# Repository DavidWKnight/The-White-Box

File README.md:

# The White Box
The White Box is a digital effect pedal for guitar and bass. It does standard effects processing such as distortion, delays, and other time based effects. Most of these effects are currently implemented in individual effect pedals, this project is attempting to put merge all these effects into a single multi effects pedal. Documentation how the design works can be found in /Documentation, The schematics for the PCB's can be found in /Hardware, and code for the processors can be found in /Software.

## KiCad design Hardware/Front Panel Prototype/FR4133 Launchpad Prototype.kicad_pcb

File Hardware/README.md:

# Hardware
The user interface is a 4x20 LCD character display, with 8 buttons and 4 knobs to interact with. These are driven by the MSP430FR45969 microcontroller which will be on a PCB referenced in the project as the "Front Panel". The front panel only deals with the user inteface and it connects to another PCB called the "Main Board" that handles all the signal processing. Signal processing is done by the C5535 DSP with the AIC3204 audio codec handling audio IO. The front panel and main board are connected by board-to-board connectors carrying 3.3v power, ground, and an SPI bus for the FR5969 and C5535 to communicate.

# CAD
Both the front panel and main board are designed using kicad which is a free PCB design suite (http://kicad-pcb.org/). Each board folder contains standard kicad project files as well as a Component Library for the custom components i've made. In each folder is also a pdf show the latest version of the schematic.

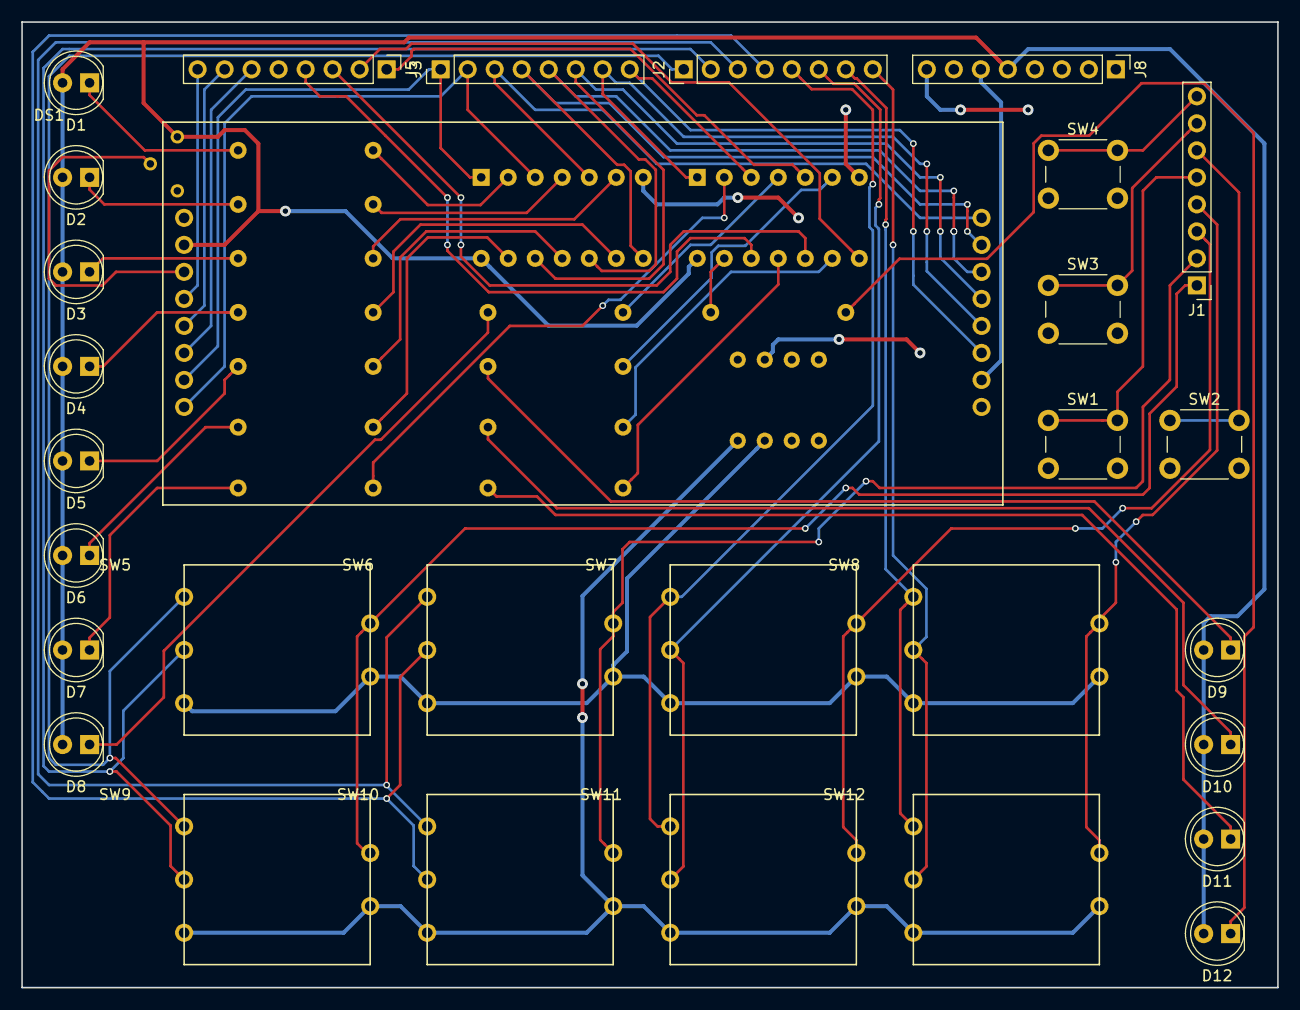
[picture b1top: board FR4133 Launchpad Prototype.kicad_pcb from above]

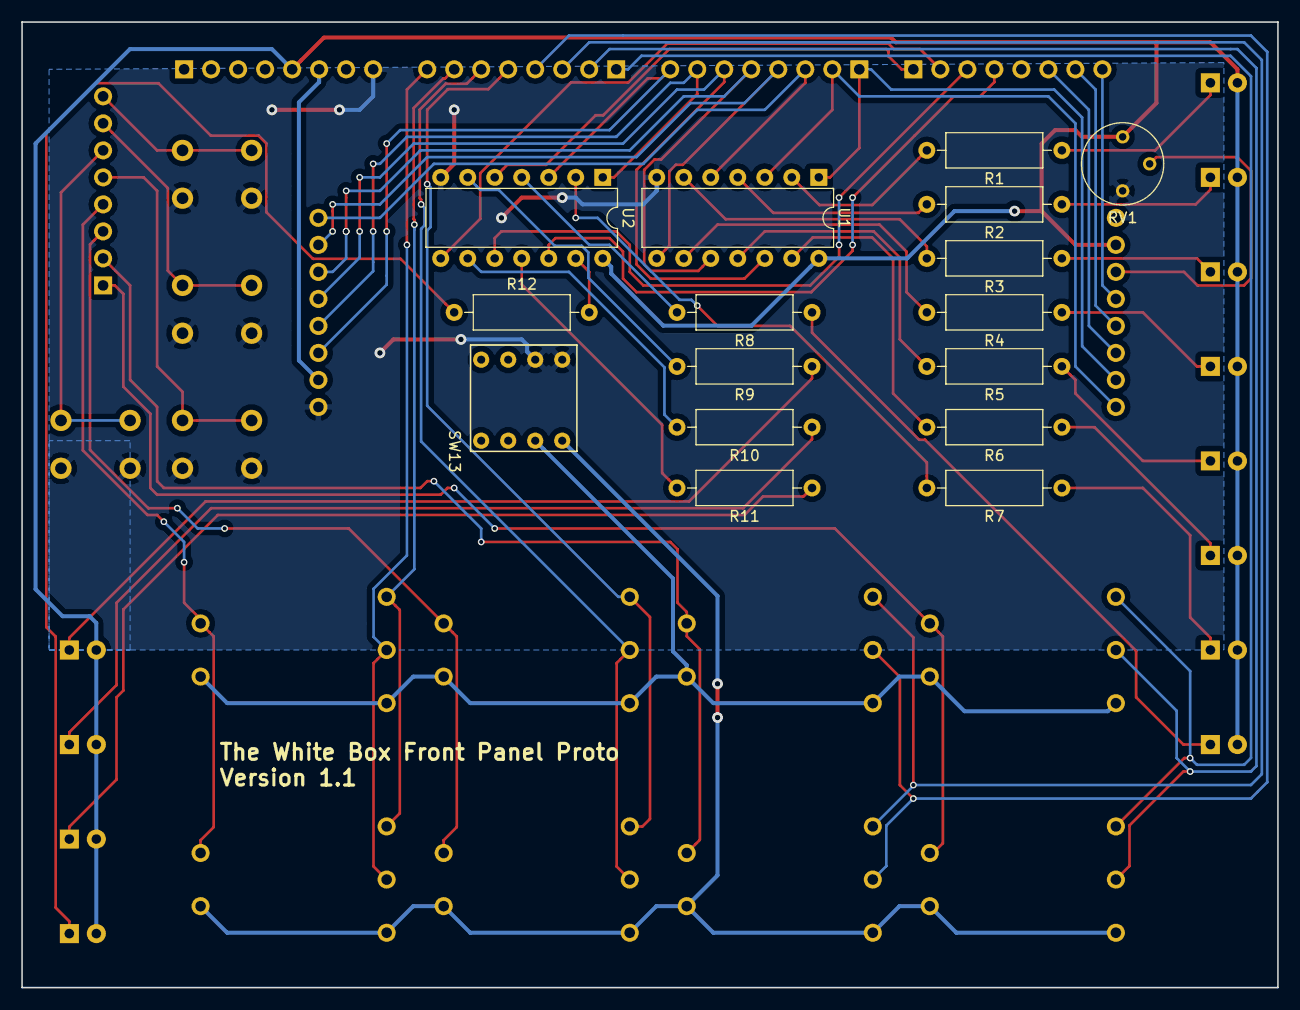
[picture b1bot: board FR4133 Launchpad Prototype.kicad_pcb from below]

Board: 2 copper layers, 118.1 x 90.8 mm, 46 parts (16 on the bottom side), 61 nets.

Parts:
D1, D2, D3, D4, D5, D6, D7, D8, D9, D10, D11, D12: LED; LED_D5.0mm
DS1: LCD-4x20; NHD-0420H1Z-FL-GBW-33V3
J1, J2, J3, J5, J8: CONN_01X08; Pin_Header_Straight_1x08_Pitch2.54mm
R1, R2, R3, R4, R5, R6, R7, R8, R9, R10, R11, R12: 100; R_Axial_DIN0309_L9.0mm_D3.2mm_P12.70mm_Horizontal
RV1: POT_TRIM; Potentiometer_Trimmer_Bourns_3339P_Horizontal
SW1, SW2, SW3, SW4: SW_Push; SW_PUSH_6mm
SW5, SW6, SW7, SW8, SW9, SW10, SW11, SW12: Rotary_Encoder_Switch; PEC16-with_SW
SW13: SW_DIP_x04; C&K-BD04
U1, U2: SN74LVC14APWR; DIP-14_W7.62mm

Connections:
+3V3: D1.2, D2.2, D3.2, D4.2, D5.2, D6.2, D7.2, D8.2, D9.2, D10.2, D11.2, D12.2, DS1.2, J8.5, RV1.1, U1.14, U2.14
/3V: DS1.15, J8.6
/12d_enc_GND: SW9.3, SW9.5, SW10.3, SW10.5, SW11.3, SW11.5, SW12.3, SW12.5, SW13.4
/24d_enc_GND: SW5.3, SW5.5, SW6.3, SW6.5, SW7.3, SW7.5, SW8.3, SW8.5, SW13.3
/P1.0: J1.1, SW5.4, SW9.4
/P1.1: J1.2, SW6.4, SW10.4
/P1.2: J1.3, SW7.4, SW11.4
/P1.3: J1.4, SW8.4, SW12.4
/P1.4: J1.5, SW1.1
/P1.5: J1.6, SW2.1
/P1.6: J1.7, SW3.1
/P1.7: J1.8, SW4.1
/P2.0: J2.1, SW5.1, SW9.1
/P2.1: J2.2, SW5.2, SW9.2
/P2.2: J2.3, SW6.1, SW10.1
/P2.3: J2.4, SW6.2, SW10.2
/P2.4: J2.5, SW7.1, SW11.1
/P2.5: J2.6, SW7.2, SW11.2
/P2.6: J2.7, SW8.1, SW12.1
/P2.7: J2.8, SW8.2, SW12.2
/P3.0: DS1.7, J3.1, U1.1
/P3.1: DS1.8, J3.2, U1.3
/P3.2: DS1.9, J3.3, U1.5
/P3.3: DS1.10, J3.4, U1.8
/P3.4: DS1.11, J3.5, U1.10
/P3.5: DS1.12, J3.6, U1.12
/P3.6: DS1.13, J3.7, U2.1
/P3.7: DS1.14, J3.8, U2.3
/P5.5: DS1.6, J5.6
/P5.6: DS1.5, J5.7
/P5.7: DS1.4, J5.8
/SN74_C: J5.1, U2.5
/SN74_D: J5.2, U2.8
/SN74_E: J5.3, U2.10
/SN74_F: J5.4, U2.12
GND: DS1.1, DS1.16, J8.8, RV1.3, SW1.2, SW2.2, SW3.2, SW4.2, SW13.5, SW13.6, U1.7, U2.7
unnamed: D1.1, R1.1
unnamed: D2.1, R2.1
unnamed: D3.1, R3.1
unnamed: D4.1, R4.1
unnamed: D5.1, R5.1
unnamed: D6.1, R6.1
unnamed: D7.1, R7.1
unnamed: D8.1, R8.1
unnamed: D9.1, R9.1
unnamed: D10.1, R10.1
unnamed: D11.1, R11.1
unnamed: D12.1, R12.1
unnamed: DS1.3, RV1.2
unnamed: R1.2, U1.2
unnamed: R2.2, U1.4
unnamed: R3.2, U1.6
unnamed: R4.2, U1.9
unnamed: R5.2, U1.11
unnamed: R6.2, U1.13
unnamed: R7.2, U2.2
unnamed: R8.2, U2.4
unnamed: R9.2, U2.6
unnamed: R10.2, U2.9
unnamed: R11.2, U2.11
unnamed: R12.2, U2.13

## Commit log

2017-01-01 Added CCS to gitignore
2017-01-01 Stated Schematic
2017-01-02 Updated gitignore
2017-01-02 added schematic for front panel
2017-01-02 edited formatting and added connector for unused pins
2017-01-02 remove .swp file
2017-01-03 added schematic for Main Board
2017-01-03 added part numbers to symbols
2017-02-24 added bettery to power supply section, added pdf plots for schematics
2017-03-10 added symbol for MSP430FR5969
2017-03-10 added FR5969, uses SPI to talk to DSP, added connections for LED/LCD brightness via PWM outputs
2017-03-11 minor changes to Front Panel Control
2017-03-13 removed 1.3v and 1.8v supplies, removed circuitry for USB connections
2017-03-13 added schematic and code for the launchpad prototype
2017-03-18 Broke debounce and state machine functions into separate functions for each port. P2 not working, should be redone from scratch
2017-03-19 Fixed P2 state machine, edited some variable names for clarity
2017-03-23 replaced components to use kicad new standard libraries
2017-03-23 Added TLV320AIC3204, I'm not sure if the signal clamping will work properly
2017-03-24 Fixed capacitor values and references for AIC3204 on Peripherals page
2017-03-24 Converted power supply to switching regulator, minor connection changes to power flags, removed bypass en
2017-03-25 added switch statements to other menu's, added pragma as example to reserve memory, Front Panel Sch is missing symbol for pushbutton
2017-03-25 Added notes to Front Panel sch to change SPI to I2C
2017-03-25 Created function menu_effect_name_edit, made small changes to other menu functions, moved effect_data struct to header
2017-03-25 moved contents of menu.c and menu.h into new files menu_support.c and menu_support.h, moved extra functions in main.c to menu.c and menu.h
2017-03-26 small changes to number of variables in array all_effects_data, moved some #define's
2017-03-30 Changed some function names
2017-03-30 Added KiCad design files for the Front Panel Prototype
2017-03-31 added functions effect_select_write_effects to write menu info of effect select menu
2017-04-07 Revised effect_select_write_effects to be more efficient
2017-04-10 added functions to load and save effect params, added functions for updating DSP and LED's, implemented these functions into menus
2017-04-10 Fixed some funtctions for Menu_Effect_Select, reduced the amount of delay and LCD Write and CMD functions
2017-04-10 LCD write data and cmd functions now remember what was on the port before writing and write that data back to the port once done
2017-04-10 Added python script to generate default all_effect_data information
2017-04-10 Tested out rotary encoders, works great, made a few bugfixes to various bits of menu logic, setup functions now clear display
2017-04-10 IT REMEMBERSgit add --allgit add --all (FRAM can now be saved to properly)
2017-04-13 Added some comments for reference later, also verified effect name edit does not work as intended
2017-04-14 Finished effect name edit, full flashing support using RTC, RTC interrupt now available for all menus
2017-04-14 Removed link to oshpark
2017-04-14 fixed through hole sizes for LCD and encoders
2017-04-15 added/edited comments for clarity
2017-04-15 Fixed clock source for RTC
2017-04-16 corrected some cannot reach errors related to #if in menu.c, removed preset_number from effect_data struct
2017-04-16 Initialized some values in all effect data to test the LED's
2017-04-18 Replaced inverters in schematic with D-latch to remove flashing during lcd write, also replaced PWM powered BJTs with MOSFETs
2017-04-19 Fixed bug where buttons wouldn't respond until after a couple presses, also accidentally fixed issue with encoder switch not being recognized
2017-04-21 Restructured menu-effect_edit to use new function effect_edit_update_FX to handle moving to a new effect and updating leds
2017-04-22 minor changes
2017-04-22 fixed some cppcheck suggestions, changed delay time during LCD_write_cmd
2017-04-22 Moved menu_effect_name_edit flashing logic into function called effect_edit_name_cursor
2017-04-23 Created LCD_write_integer function and created support functions for menu_settings
2017-04-23 fixes brightness controls on schematic, LED brightness now connects to OE on D latch
2017-04-24 reworked LCD_write_integer function and integrated it into menu_effect_edit
2017-04-24 Added cursor flashing to settings menu
2017-04-25 created function effect_edit_change_param, fixed big when leaving menu_effect_edit w/o saving
2017-04-25 added more documentation for functions
2017-04-25 Fixed bug where RTC flag would be enabled when leaving menus causing errors when writing new menus to the lcd
2017-04-28 small changes to front panel schematic
2017-05-01 moved debounce routines to both use TA0, TA1 is now used for controlling brightness, works properly for CCR2 controlling LED's
2017-05-08 restructured the location of some #include statements
2017-05-16 Removed folder/schematic '/Software/Front Panel Launchpad'
2017-05-16 Implemented brightness control for LCD
2017-05-16 Fixed some mistakes on Front Panel Schematic
2017-05-17 updated TLV connection to DSP
2017-05-18 plotted main panel schematic pdf
2017-06-10 Initial commit for c5535 ezDSP in software folder, project currently gets audio from the stereo input and sends it to the stereo output on the ezDSP
2017-06-11 added readme to c5535 ezdsp, includes TI copyright info
2017-06-11 Split menu and menu_support into separate files to make more sense, moved some functions around to make more logical sense
2017-06-11 Changed scope of some variables to be more localized
2017-06-14 minor changes to projects
2017-06-14 added python/c++ code for adding effects to wav files
2017-06-14 changed a file name and the README to make more sense
2017-06-14 modified I2S read/write to check for correct flags before continuing
2017-06-28 edited scope of functions in FP launchpad
2017-06-28 added exe's to gitignore
2017-06-30 Changed author name in source files to David Knight
2017-07-02 Found there is corrupted memory at circ_buffer_sig range 39630-39830, causes a clicking sound during play
2017-07-04 Added tremolo and digital filtering functions to c55 code, also fixed the flange effect to actually work
2017-07-04 added resource used for DSP
2017-07-04 .h files now count as c files rather than c++
2017-07-22 update gitignore for vscode
2017-07-22 update gitignore
2017-07-22 add .vscode to gitignore
2017-07-22 removed .vscode
2017-08-01 Revised effect functions and rearragned memory allocation in c55
2017-08-02 removed my_math.h include in ezDSP/effects.h
2017-08-03 Removed floating point math from ezdsp/effects.c
2017-08-11 Removed time based effects from main
2017-08-11 I'm really bad at git, something went wrong with my commit history, hopefully this fixes it
2017-08-11 Reorganised front panel code folder, removed Front panel prototype
2017-08-11 Create UI.txt
    Created the documentation for the LCD UI
2017-08-11 Update README.md
    Clarification on goal and what each subfolder contains
2017-08-12 Create Front Panel.txt
    Added information on how the code is supposed to work and how the front panel hardware is setup.
2017-08-12 Renamed some variables and added some comments, no changes to code logic
2017-09-15 Added fixed point math routines, implemented fixed point delay and flange effects
2017-09-15 Removed old floating point effects, commented out effects currently using floating point math
2017-09-15 Removed commented out effects in main loop, and uncommented PLL_init
2017-09-17 Redid input processing for msp430, much simpler and more reliable
2017-09-17 Added RTC interrupt to wait_for_input function
2017-09-17 Update Front Panel.txt
    Updated documentation for how user inputs are processed
2017-09-18 consolidated C5535 folders that had different capitalization
